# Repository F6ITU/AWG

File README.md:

# AWG
poor man's function generator

Ce projet est une stricte copie du générateur de signaux complexes à base de raspberry pi zero (processeur 2040)
publié par Wolf2018 https://www.instructables.com/Poor-Mans-Waveform-Generator-Based-on-RP2040-Raspb/ 

lui même dérivé du projet rgco https://www.instructables.com/Arbitrary-Wave-Generator-With-the-Raspberry-Pi-Pic/ 
reposant sur un raspberry pi pico (processeur 2020)

Les droits sont détenus par l'éditeur Autodesk, il s'agit donc d'un projet "publié" mais non open source, non open hardware, 
totalement "propriétarisé" par l'éditeur. 

Les firmwares et instructions de montage sont à récupérer sur le site instructable, et ne peuvent être intégré sur ce dépot

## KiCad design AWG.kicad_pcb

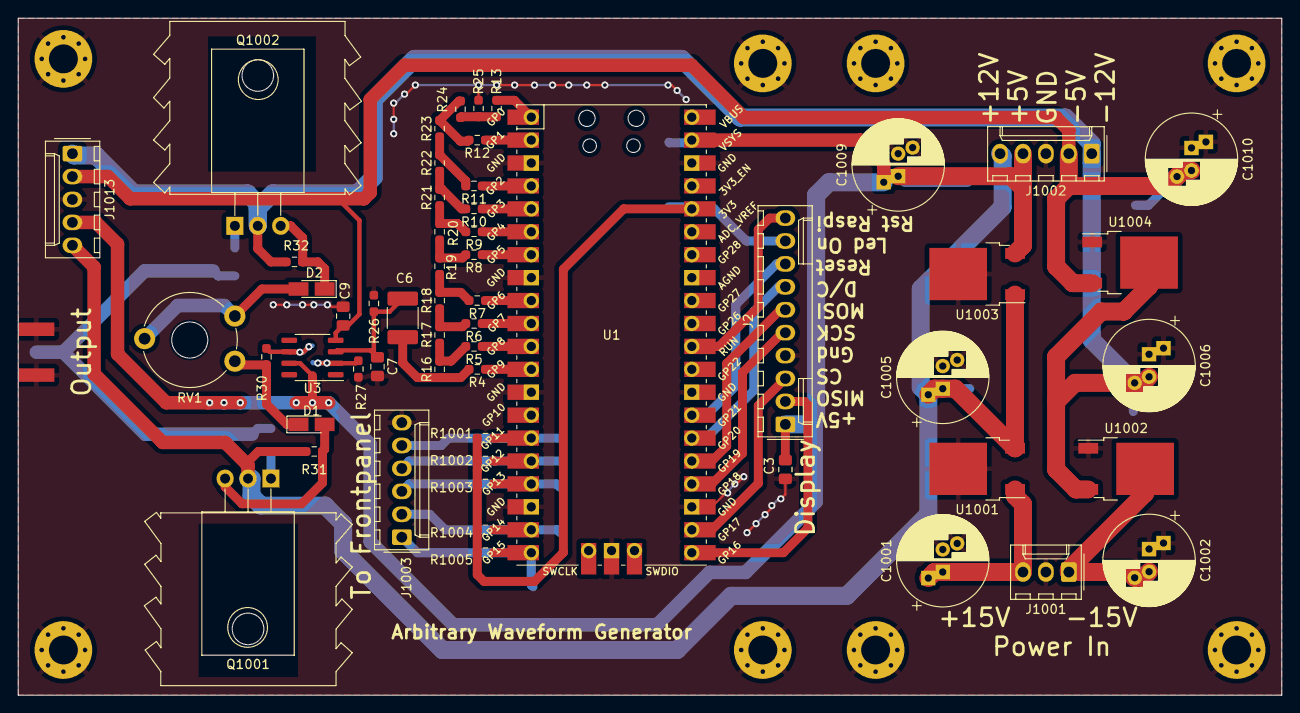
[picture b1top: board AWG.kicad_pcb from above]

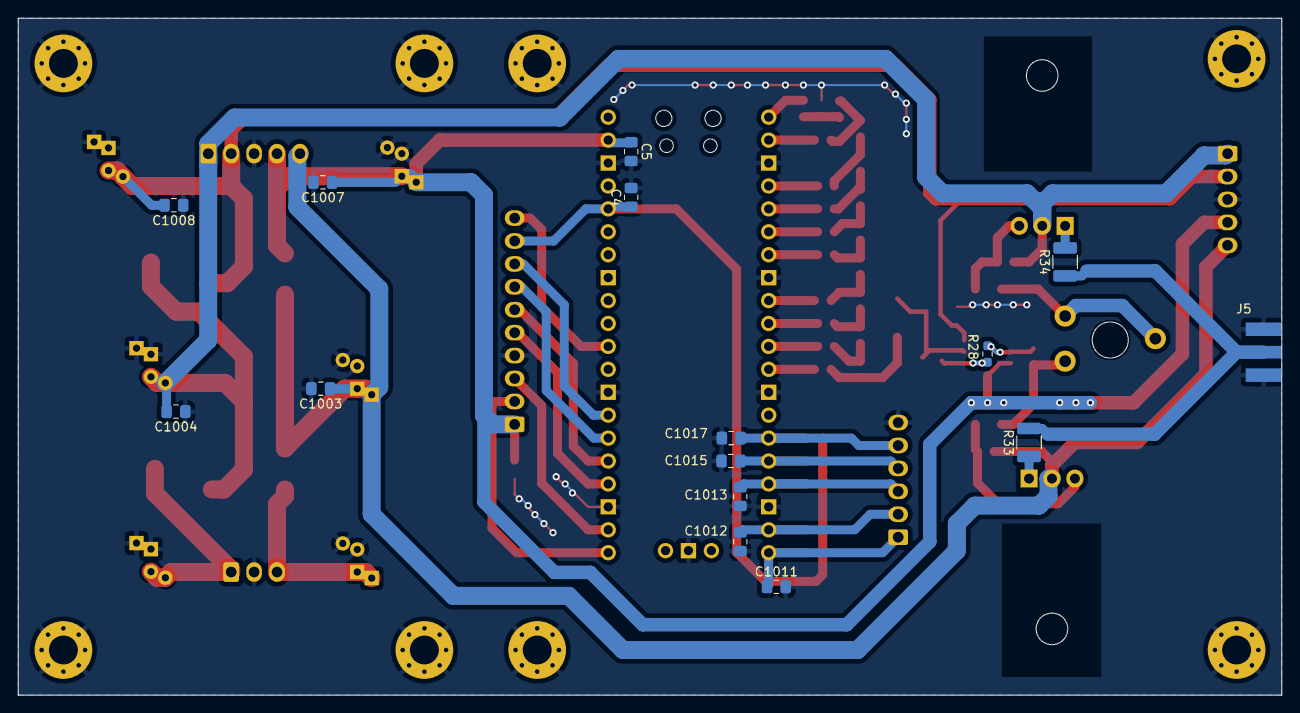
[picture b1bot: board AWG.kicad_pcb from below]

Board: 2 copper layers, 140.0 x 75.0 mm, 81 parts (15 on the bottom side), 50 nets.

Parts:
C3, C4, C5, C9, C1003, C1004, C1007, C1008, C1011, C1012, C1013, C1015, C1017: 100n; C_0805_2012Metric_Pad1.18x1.45mm_HandSolder
C6: 1mF; C_1812_4532Metric_Pad1.57x3.40mm_HandSolder
C7: 3.3p; C_0805_2012Metric_Pad1.18x1.45mm_HandSolder
C1001, C1002, C1005, C1006, C1009, C1010: 100u 50V; CP_Radial_D10.0mm_P2.50mm_P5.00mm
D1, D2: 4148; D_MicroMELF_Handsoldering
HS1001, HS1002: Heatsink; Heatsink_Aavid-TV5G_TO220_Horizontal
J2: Conn afficheur; Molex_KK-254_AE-6410-10A_1x10_P2.54mm_Vertical
J5: SMA; SMA_EDGE_NRW
J1001: Conn_01x03; Molex_KK-254_AE-6410-03A_1x03_P2.54mm_Vertical
J1002, J1013: Conn_01x05; Molex_KK-254_AE-6410-05A_1x05_P2.54mm_Vertical
J1003: Conn_01x06; Molex_KK-254_AE-6410-06A_1x06_P2.54mm_Vertical
J1005, J1006, J1007, J1008, J1009, J1010, J1011, J1012: Conn_01x01; MountingHole_3.2mm_M3_Pad_Via
Q1001: NTE2633; TO-220-3_Horizontal_TabDown
Q1002: NTE2634; TO-220-3_Horizontal_TabDown
R4, R5, R6, R7, R8, R9, R10, R11, R12, R13, R25: 2k; R_0603_1608Metric_Pad0.98x0.95mm_HandSolder
R16, R17, R18, R19, R20, R21, R22, R23, R24, R31, R32, R1001, R1002, R1003, R1004, R1005: 1k; R_0603_1608Metric_Pad0.98x0.95mm_HandSolder
R26: 20k; R_0603_1608Metric_Pad0.98x0.95mm_HandSolder
R27, R28: 680R; R_0603_1608Metric_Pad0.98x0.95mm_HandSolder
R30: 27R; R_0603_1608Metric_Pad0.98x0.95mm_HandSolder
R33, R34: 3R3; R_1210_3225Metric_Pad1.30x2.65mm_HandSolder
RV1: 100R; Potentiometer_Piher_PT-10-V10_Vertical_Hole
U1: Pico; RPi_Pico_SMD_TH
U3: AD8055ARZ; SO-8_3.9x4.9mm_P1.27mm
U1001: L7812; TO-252-2
U1002: L7912; TO-252-2
U1003: L7805; TO-252-2
U1004: L7905; TO-252-2

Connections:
+3V3: C4.1, J2.9, R1001.2, R1002.2, R1003.2, R1004.2, R1005.2, U1.36 (3V3)
+5V: C3.1, C5.1, C1007.1, C1009.1, J2.1, J1002.4, J1013.4, U1.39 (VSYS), U3.7 (VS+), U1003.3 (OUT)
+12V: C1003.1, C1005.1, J1002.5, J1013.5, Q1001.2 (C), R31.1, U1001.3 (OUT), U1003.1 (IN)
-5V: C9.2, C1008.2, C1010.2, J1002.2, J1013.2, U3.4 (VS-), U1004.3 (VO)
-12V: C1004.2, C1006.2, J1002.1, J1013.1, Q1002.2 (C), R32.2, U1002.3 (VO), U1004.2 (VI)
GND: C3.2, C4.2, C5.2, C7.2, C9.1, C1001.2, C1002.1, C1003.2, C1004.1, C1005.2, C1006.1, C1007.2, C1008.1, C1009.2, C1010.1, C1011.2, C1012.2, C1013.2, C1015.2, C1017.2, J2.4, J5.2 (Ext), J1001.2, J1002.3, J1003.6, J1005.1, J1006.1, J1007.1, J1008.1, J1009.1, J1010.1, J1011.1, J1012.1, J1013.3, R25.2, R26.2, R27.2, U1.3 (GND), U1.8 (GND), U1.13 (GND), U1.18 (GND), U1.23 (GND), U1.28 (GND), U1.38 (GND), U1.42 (GND), U1001.2 (GND), U1002.1 (GND), U1003.2 (GND), U1004.1 (GND)
unnamed: C6.1, C7.1, R26.1, U3.3 (IN+)
unnamed: C6.2, R4.2, R16.1
unnamed: C1001.1, J1001.3, U1001.1 (IN)
unnamed: C1002.2, J1001.1, U1002.2 (VI)
unnamed: C1011.1, J1003.1, R1005.1, U1.20 (GPIO15)
unnamed: C1012.1, J1003.2, R1004.1, U1.19 (GPIO14)
unnamed: C1013.1, J1003.3, R1003.1, U1.17 (GPIO13)
unnamed: C1015.1, J1003.4, R1002.1, U1.16 (GPIO12)
unnamed: C1017.1, J1003.5, R1001.1, U1.15 (GPIO11)
unnamed: D1.1 (K), R30.2, RV1.3
unnamed: D1.2 (A), Q1001.3 (B), R31.2
unnamed: D2.1 (K), Q1002.3 (B), R32.1
unnamed: D2.2 (A), RV1.1, RV1.2
unnamed: J2.2, U1.21 (GPIO16)
unnamed: J2.3, U1.22 (GPIO17)
unnamed: J2.5, U1.24 (GPIO18)
unnamed: J2.6, U1.25 (GPIO19)
unnamed: J2.7, U1.26 (GPIO20)
unnamed: J2.8, U1.27 (GPIO21)
unnamed: J2.10, U1.30 (RUN)
unnamed: J5.1 (In), R33.2, R34.1
unnamed: Q1001.1 (E), R33.1
unnamed: Q1002.1 (E), R34.2
unnamed: R4.1, U1.12 (GPIO9)
unnamed: R5.1, U1.11 (GPIO8)
unnamed: R6.1, U1.10 (GPIO7)
unnamed: R7.1, U1.9 (GPIO6)
unnamed: R8.1, U1.7 (GPIO5)
unnamed: R9.1, U1.6 (GPIO4)
unnamed: R10.1, U1.5 (GPIO3)
unnamed: R10.2, R21.2, R22.1
unnamed: R11.1, U1.4 (GPIO2)
unnamed: R11.2, R22.2, R23.1
unnamed: R12.1, U1.2 (GPIO1)
unnamed: R12.2, R23.2, R24.1
unnamed: R13.1, U1.1 (GPIO0)
unnamed: R13.2, R24.2, R25.1
unnamed: R5.2, R16.2, R17.1
unnamed: R6.2, R17.2, R18.1
unnamed: R7.2, R18.2, R19.1
unnamed: R8.2, R19.2, R20.1
unnamed: R9.2, R20.2, R21.1
unnamed: R27.1, R28.1, U3.2 (IN-)
unnamed: R28.2, R30.1, U3.6 (VOUT)

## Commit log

2021-12-09 version initiale, schema saisi, pcb en cours
2021-12-09 new frontplate interface circuit, new power distrib
2021-12-10 interface, power supply & transistor pinout corrected
2021-12-10 schematic added
2021-12-10 last BOM reference added
2021-12-10 D2Pack linear regulator added
2021-12-10 3D shapes added
2021-12-11 heatsink added
2021-12-11 routing done
2021-12-12 auxiliary power connector added
2021-12-12 1mf non polar cap added
2021-12-12 minor cosmetic details.Bypass cap changed
2021-12-13 schematic and 3Dview added in documents folder
2021-12-15 iBOM added
2021-12-19 shorter track for R28
2022-07-21 R33-R34 format changed to 1210
2023-12-01 minor changes, kicad 7 update
2023-12-02 unlocked ? who knows...
